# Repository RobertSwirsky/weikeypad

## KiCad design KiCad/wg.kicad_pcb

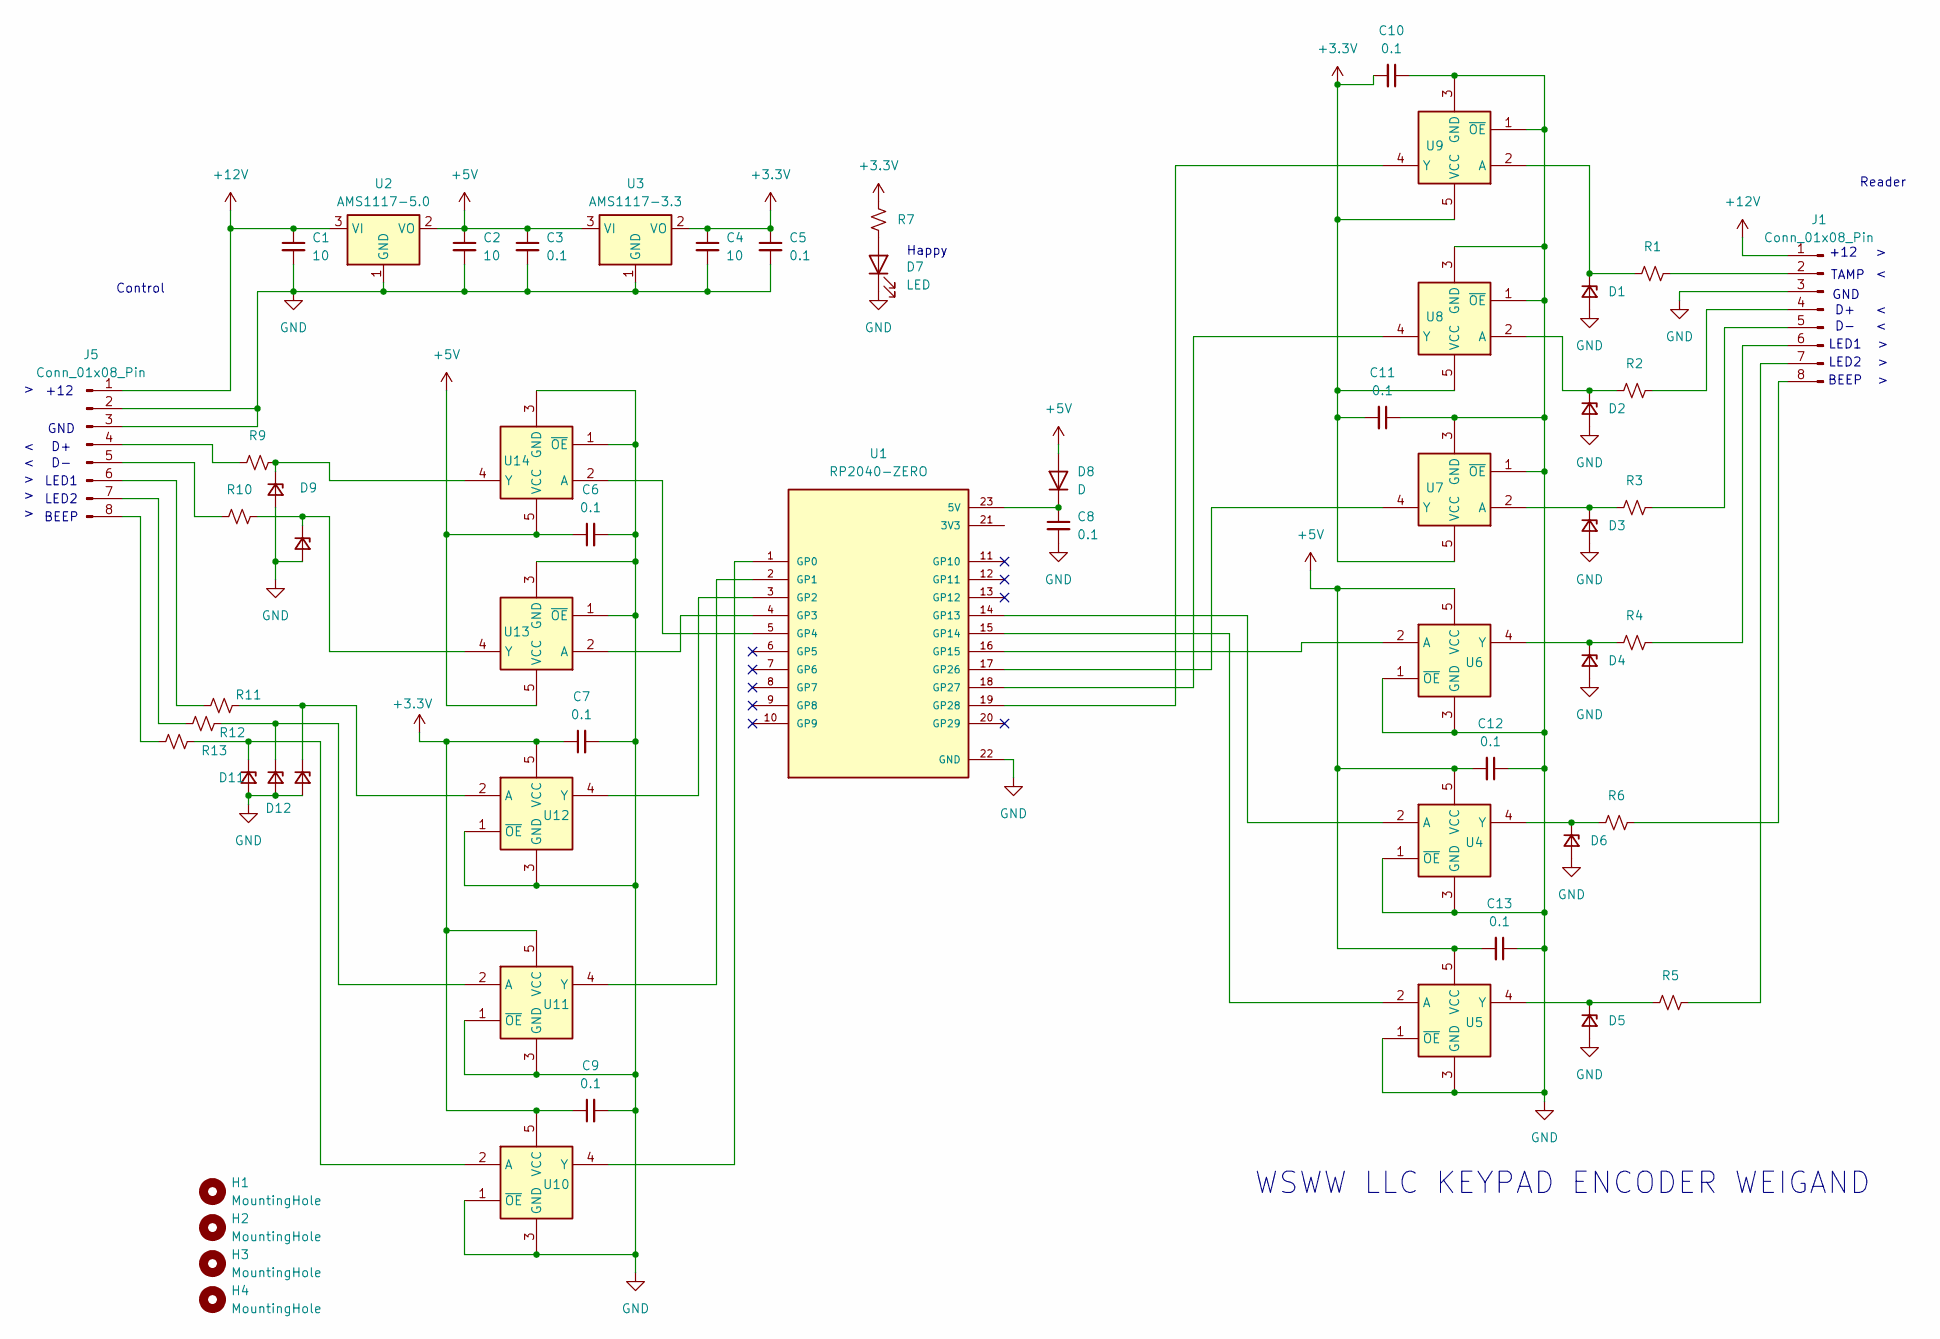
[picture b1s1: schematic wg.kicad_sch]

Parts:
C1, C2, C4: 10; CP_Radial_D4.0mm_P2.00mm
C3, C5, C6, C7, C8, C9, C10, C11, C12, C13: 0.1; C_Disc_D3.0mm_W1.6mm_P2.50mm
D1, D2, D3, D4, D5, D6, D9, D10, D11, D12, D13: D_Zener_Small; D_SOD-323_HandSoldering
D7: LED; R_1206_3216Metric_Pad1.30x1.75mm_HandSolder
D8: D
H1, H2, H3, H4: MountingHole; MountingHole_3mm
J1, J5: Conn_01x08_Pin; PhoenixContact_MC_1,5_8-G-3.5_1x08_P3.50mm_Horizontal
R1, R2, R3, R4, R5, R6, R7, R9, R10, R11, R12, R13: R_Small_US; R_1206_3216Metric_Pad1.30x1.75mm_HandSolder
U1: RP2040-ZERO; MODULE_RP2040-ZERO; PARTREV NA
U2: AMS1117-5.0; SOT-223-3_TabPin2
U3: AMS1117-3.3; SOT-223-3_TabPin2
U4, U5, U6, U7, U8, U9, U10, U11, U12, U13, U14: NC7SZ125M5X; SOT-23-5

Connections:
+3.3V: C4.1, C5.1, C7.1, C9.1, C10.2, C11.2, R7.2, U3.2 (VO), U7.5 (VCC), U8.5 (VCC), U9.5 (VCC), U10.5 (VCC), U11.5 (VCC), U12.5 (VCC)
+12V: C1.1, J1.1, J5.1, U2.3 (VI)
GND: C1.2, C2.2, C3.2, C4.2, C5.2, C6.2, C7.2, C8.2, C9.2, C10.1, C11.1, C12.1, C13.1, D1.2 (A), D2.2 (A), D3.2 (A), D4.2 (A), D5.2 (A), D6.2 (A), D7.1 (K), D9.2 (A), D10.2 (A), D11.2 (A), D12.2 (A), D13.2 (A), J1.3, J5.2, J5.3, U1.22 (GND), U2.1 (GND), U3.1 (GND), U4.1 (~OE), U4.3 (GND), U5.1 (~OE), U5.3 (GND), U6.1 (~OE), U6.3 (GND), U7.1 (~OE), U7.3 (GND), U8.1 (~OE), U8.3 (GND), U9.1 (~OE), U9.3 (GND), U10.1 (~OE), U10.3 (GND), U11.1 (~OE), U11.3 (GND), U12.1 (~OE), U12.3 (GND), U13.1 (~OE), U13.3 (GND), U14.1 (~OE), U14.3 (GND)
unnamed: D1.1 (K), R1.1, U9.2 (A)
unnamed: D2.1 (K), R2.1, U8.2 (A)
unnamed: D3.1 (K), R3.1, U7.2 (A)
unnamed: D4.1 (K), R4.1, U6.4 (Y)
unnamed: D5.1 (K), R5.1, U5.4 (Y)
unnamed: D6.1 (K), R6.1, U4.4 (Y)
unnamed: D7.2 (A), R7.1
unnamed: D9.1 (K), R9.2, U14.4 (Y)
unnamed: D10.1 (K), R10.2, U13.4 (Y)
unnamed: D11.1 (K), R13.2, U10.2 (A)
unnamed: D12.1 (K), R12.2, U11.2 (A)
unnamed: D13.1 (K), R11.2, U12.2 (A)
unnamed: J1.2, R1.2
unnamed: J1.4, R2.2
unnamed: J1.5, R3.2
unnamed: J1.6, R4.2
unnamed: J1.7, R5.2
unnamed: J1.8, R6.2
unnamed: J5.4, R9.1
unnamed: J5.5, R10.1
unnamed: J5.6, R11.1
unnamed: J5.7, R12.1
unnamed: J5.8, R13.1
unnamed: U1.1 (GP0), U10.4 (Y)
unnamed: U1.2 (GP1), U11.4 (Y)
unnamed: U1.3 (GP2), U12.4 (Y)
unnamed: U1.4 (GP3), U13.2 (A)
unnamed: U1.5 (GP4), U14.2 (A)
unnamed: U1.14 (GP13), U4.2 (A)
unnamed: U1.15 (GP14), U5.2 (A)
unnamed: U1.16 (GP15), U6.2 (A)
unnamed: U1.17 (GP26), U7.4 (Y)
unnamed: U1.18 (GP27), U8.4 (Y)
unnamed: U1.19 (GP28), U9.4 (Y)

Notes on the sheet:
LED2
LED1
+12
Reader
TAMP
Happy
GND
BEEP
Control
WSWW LLC KEYPAD ENCODER WEIGAND

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
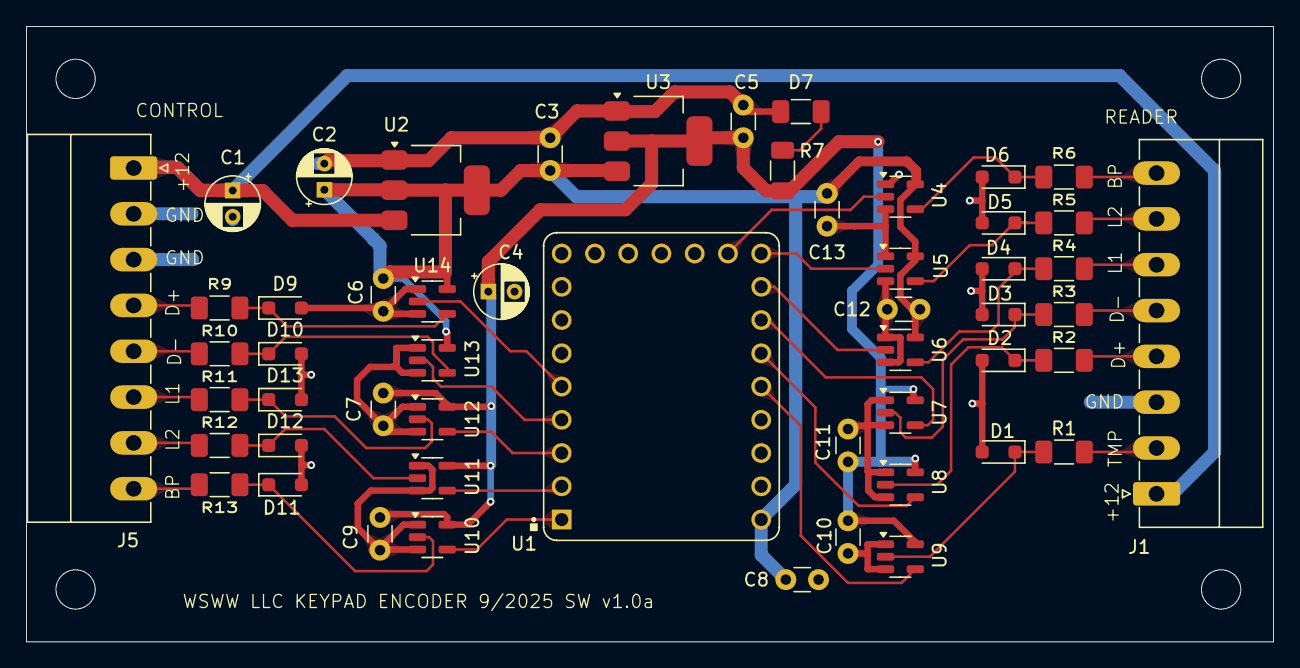
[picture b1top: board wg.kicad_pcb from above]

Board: 2 copper layers, 95.2 x 47.0 mm, 57 parts (0 on the bottom side), 38 nets.

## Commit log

2025-02-07 First pass at reading Weigand with PIO
2025-02-07 Initial bugfixes for Micropython syntax
2025-02-07 Removed debug prints
2025-02-07 Set pull-up/down values correctly. Clear ISR if no bits
2025-02-07 Check for fifo contents
2025-02-08 Trying different pullup/down options Switched to pin 16/17
2025-02-10 Now reliably reading Weigand cards
2025-02-12 Parity checking and hex representation
2025-02-12 Parity calculation
2025-02-26 Transmit routine
2025-02-27 Transmit code
2025-02-27 Debugging transmit code
2025-02-27 Fix transmit code -- active high
2025-02-27 Weigand TX code running
2025-03-02 Don't consider last bit when looking at hex
2025-03-02 Convert 6 digit keypad codes to 37-bit weigand
2025-03-07 Treat keypad input not as BCD but as binary decimal number
2025-04-02 Test of Micropython timers
2025-04-07 Timeout in 6 seconds if code not entered in time
2025-04-07 Timeout code
2025-04-08 Remapped pins
2025-04-08 Timeout if six digits not received in six seconds
2025-04-08 Timeout code; scan in a badge overrides accumulation of digits
2025-07-02 Handle a badge after a key is pressed
2025-07-02 Clear accumulated bits after timeout
2025-07-02 Refactor ClearAccumulatedBits
2025-07-02 Refactor ClearAccumulatedBit
2025-07-02 Don't send a "zero" packet if the user just hits # or *
2025-09-05 Added schematic
2025-09-10 Moved I/O pins to match latest schematic
2025-10-16 Changed I/O to match latest schematic
2025-10-16 Added iotest program
2025-10-16 Changed Pull_up to pull down on iotest
2025-10-16 Fixed pin assignments
2025-10-17 Fixed typo in weikepad
2025-10-17 Added in KiCad project
2025-10-21 Clearl any accumulated keypad digits if a badge scan is detected
2025-10-22 Added test code for LED, BEEP
2025-10-22 LED Control
2025-11-04 .gitignore fore KiKad stuff
2025-11-13 Sync the LED and BEEP lines from the controller with the keypad
2025-12-18 Design for 3D printable case
2026-01-13 Updated design for 3D printable case for the openings for the wires
2026-01-14 Test of "tamper" code
2026-01-14 Tamper ISR
2026-01-14 More tamper code. Don't do any more non-blocking PIO fifo calls so I can look for tamper
2026-01-16 Tamper interrupt code -- three possible scenarios
2026-01-17 Tamper code. Send "f000911"
2026-01-17 Remove pull-up from tamper pin
2026-01-18 Fixed box to put screwholes on top
2026-01-19 put the screwholes in the top
2026-01-19 Update for holes on top, high quality print mode, 30% infil
2026-01-20 Made the fill denser
2026-02-12 Send a different code F000911 or F000912 depending on whether tamper is set or cleared
2026-02-12 Fixed misleading comment
